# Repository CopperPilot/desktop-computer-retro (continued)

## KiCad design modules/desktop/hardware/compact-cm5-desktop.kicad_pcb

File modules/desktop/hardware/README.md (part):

# KiCad Project — Compact All-in-One CM5 Desktop Computer (`main` Carrier Board)

Generated from `rea/spec.yaml` by rea-hardware (fab rules, stackup, outline at the origin, mounting
holes), then completed by the electrical agent. Every placed part carries a verified `LCSC` field.

## 1. Component Rating & Margin Verification

| Component / Group | Net / Rail | Max Rail Voltage / Peak Current | Part MPN (`LCSC`) | Datasheet Rating | Margin Check |
|---|---|---|---|---|---|
| `C_PD_IN` | `VBUS_IN` (unswitched `J_PWR` VBUS) | 15.0 V nominal (24.4 V surge clamp) | `CC0805KKX7R9BB105` (`C91185`, 1 uF 50 V X7R 0805) | 50 V X7R | 50 V = 3.33x of 15 V (> 24.4 V TVS clamp); keeps unswitched `J_PWR` `cSnkVBus` = 1.0 uF direct (2.0 uF total including `C_PD_VHV` behind 1 kOhm `R_PD_VHV`), well below the 10 uF USB Type-C limit |
| `Q_PD_SW` + `R_PD_PG` + `R_PD_PG2` + `C_PD_SS` | `VBUS_IN` -> `VBUS_PD` (15 V PD) | 15.0 V / 1.85 A peak (24.4 V surge clamp) | `AO3407A` (`C347478`, SOT-23) + 2x `0402WGF1003TCE` (`C25741`, 100k) + `CL05B104KB54PNC` (`C307331`, 100 nF 50 V) | `AO3407A`: -30 V `V_DS`, ±20 V `V_GS`, -4.2 A continuous, `R_DS(on)` = 37 mOhm typ at -10 V / 42 mOhm at -7.5 V (`P_D` = 1.4 W) | `R_PD_PG`=100k and `R_PD_PG2`=100k set `V_GS` = -7.50 V at 15 V (-12.2 V max at 24.4 V TVS clamp << ±20 V `V_GS(max)`) with `tau_G` = 5.0 ms soft-start (`C_PD_SS`=100 nF), isolating 67.1 uF (`C_PD_BULK` + `C_VIN1..3`) until `U_PD` `PG` asserts low |
| `C_PD_BULK` | `VBUS_PD` (switched 15 V PD) | 15.0 V nominal (24.4 V surge clamp) | `CA55-D035K476TE150` (`C2761441`, 47 uF 35 V Case-D 7343 tantalum, 150 mOhm ESR) | 35 V MnO2 tantalum | 35 V = 2.33x of 15 V (> 24.4 V TVS clamp); isolated behind `Q_PD_SW` during hot-plug and PD negotiation |
| `C_VIN1`, `C_VIN2` | `VBUS_PD` (switched 15 V PD) | 15.0 V nominal (24.4 V surge clamp) | `HGC0805R5106K350NSLJ` (`C33546007`, 10 uF 0805) | 35 V X5R | 35 V >= 2.33x of 15 V (> 24.4 V TVS clamp); isolated behind `Q_PD_SW` until PD negotiation completes |
| `C_VIN3`, `C_BUCK_BST`, `C_BUCK_EN` | `VBUS_PD` / `BUCK_BST` / `BUCK_EN` | 15.0 V / 18.3 V / 2.5 V | `CL05B104KB54PNC` (`C307331`, 100 nF 0402) | 50 V X7R | 50 V >= 2.73x of 18.3 V (> 27.7 V surge) |
| `C_PD_VHV`, `C_BUCK_VREG` | `PD_VHV` / `BUCK_VREG5` | 14.2 V / 3.3 V | `CL10A105KB8NNNC` (`C15849`, 1 uF 0603) | 50 V / 25 V X5R | `C_PD_VHV` isolated from `VBUS_IN` via `R_PD_VHV` = 1 kOhm (`0402WGF1001TCE`, `C11702`) per CH224A datasheet |
| `C_5V1..C_5V3` | `5V_SYS` | 5.0 V max | `C2012X5R1A476MTJ00E` (`C76636`, 47 uF 0805) | 10 V X5R | 3x 47 uF = 141 uF nominal (~70 uF effective at 5 V) adjacent to `L_BUCK.2` / `U_BUCK.9` |
| `C_CM5_BULK` | `5V_SYS` (at `U_CM5` pins 77-87) | 5.0 V max | `SA11AM101A19R15XXX` (`C135491`, 100 uF Case-A polymer, 15 mOhm ESR) | 10 V solid polymer | 10 V = 2.0x of 5 V; buffers CM5 3.0 A load steps directly at mezzanine socket |
| `C_3V3_IN`, `C_3V3_OUT1`, `C_3V3_OUT2`, `C_BL_IN`, `C_3V3_1`, `C_KB_VBUS`, `C_MOUSE_VBUS` | `5V_SYS`, `3V3_SYS`, `3V3_CM5`, `5V_USB_*` | <= 5.0 V max | `HGC0805R5106K350NSLJ` (`C33546007`, 10 uF 0805) | 35 V X5R | 35 V >= 7.0x of 5 V (>= 1.5x required) |
| `C_BL_COMP` | `BL_COMP` | <= 3.3 V max | `TCC0402X7R224K250AT` (`C915854`, 220 nF 0402) | 25 V X7R | Matches TPS61165 datasheet 220 nF COMP requirement |
| `C_BL_OUT` | `BL_LED_A` (LED string) | ~9.9 V typ (38 V OVP) | `CC0805KKX7R9BB105` (`C91185`, 1 uF 50 V X7R 0805) | 50 V X7R | 50 V = 1.32x above 38 V OVP cutoff |
| `C_5V4`, `C_CM5_5V`, `C_3V3_2`, `C_3V3_3`, `C_3V3_HF`, `C_CM5_1V8`, `C_BOOT_VBUS`, `C_KB_DEC`, `C_MOUSE_DEC`, `C_CC_KB`, `C_CC_MOUSE`, `C_DSI_3V3`, `C_HDMI_5V` | `5V_SYS` / `3V3_SYS` / `3V3_CM5` / `1V8_CM5` | <= 5.0 V max | `CL05B104KB54PNC` (`C307331`, 100 nF 0402) | 50 V X7R | 50 V >= 10.0x of 5 V |
| `C_BUCK_SS` | `BUCK_SS` | 3.3 V max | `0402B223K500NT` (`C1532`, 22 nF 0402) | 50 V X7R | Programs `t_SS = 22 nF * 0.6 V / 6 uA = 2.2 ms` soft-start |
| `U_PD` + `R_PD_CFG1` + `R_PD_VHV` | `VBUS_IN`, `CC1`, `CC2`, `PD_CFG1`, `PD_VHV` | 15.0 V PD | `CH224A` (`C42459160`) + `RC0402FR-0756KL` (`C114756`, 56 kOhm 1%) + `0402WGF1001TCE` (`C11702`, 1 kOhm 1%) | 4 V to 30 V operating (`VHV` pin 1 fed from `VBUS_IN` via `R_PD_VHV` = 1 kOhm `C11702` + 1 uF `C_PD_VHV` per CH224A application circuit); `CFG1` (pin 9) strapped to `GND` via `R_PD_CFG1` = 56 kOhm 1% (`C114756`) to request mandatory 15 V USB-PD 3.0 fixed PDO | 30 V max > 24.4 V TVS clamp on 15 V rail; 56 kOhm requests 15 V (1.85 A peak at 27.71 W input < 3.0 A PDO limit) |
| `U_BUCK` + `L_BUCK` + `C_BUCK_EN` | `VBUS_PD` -> `5V_SYS` | 15.0 V in (24.4 V surge clamp), 5.0 V / 4.89 A peak | `SY8205FCC` (`C111875`) + `PSPMAA0503-4R7M-ANP` (`C436535`) + `CL05B104KB54PNC` (`C307331`) | 4.5-30 V recommended operating / 33 V abs max input, 5.0 A continuous / 6.0 A peak (`V_REF` = 0.600 V; `R_BUCK_FB1`=73.2k `C26986` / `R_BUCK_FB2`=10k `C25744` -> `V_OUT` = 4.992 V); `R_BUCK_EN1`=100k / `R_BUCK_EN2`=20k + `C_BUCK_EN`=100 nF on switched `VBUS_PD` sets `V_BUCK_EN` = 2.50 V at 15.0 V (`>= 2.38 V` at 14.25 V > `V_ENH` = 1.2 V) with `tau_EN` = 1.67 ms RC delay after `Q_PD_SW` charges `VBUS_PD` | 30 V rec / 33 V abs max safely exceeds `D_PD_VBUS` (`PTVS15VS1UR,115`, `V_BR`=16.7-18.5 V, `V_CL`=24.4 V at 16.4 A); `Q_PD_SW` isolates `VBUS_PD` until `U_PD.10` (`PG`) asserts |
| `U_3V3` + `L_3V3` + `Q_3V3_INV` + `Q_3V3_DIS` + `R_3V3_DIS` + `R_3V3_BLEED` + `D_3V3_CLAMP` + `U_SW_DSI` + `R_DSI_DIS` | `5V_SYS` -> `3V3_SYS` -> `3V3_DSI` | 3.3 V / 0.55 A peak (`front_io` + `J_DSI.22`) | `TLV62569DBVR` (`C141836`) + `SPH4018H2R2MT` (`C370436`, 2.2 uH) + 2x `BSS138` (`C78284`) + `0402WGF330JTCE` (`C25105`, 33R) + `0402WGF1001TCE` (`C11702`, 1k) + `B5819W` (`C2943878`) + `TPS2051BDBVR` (`C24593`) | `TLV62569DBVR`: 2.5-5.5 V in, 2.0 A out (`R_3V3_FB1`=100k `C25741` / `R_3V3_FB2`=22.1k `C43473` -> `V_OUT` = 3.31 V), enabled by `3V3_CM5`; active discharge (`Q_3V3_INV`/`Q_3V3_DIS` + `R_3V3_DIS`=33R + `R_3V3_BLEED`=1k, `tau` = 1.85 ms) and `D_3V3_CLAMP` (`B5819W` Anode `3V3_SYS` -> Cathode `3V3_CM5`) clamp `3V3_SYS <= 3V3_CM5 + 0.25 V` during shutdown/reset; `TPS2051BDBVR`: 500 mA soft-start load switch gating `J_DSI.22` (`3V3_DSI`) via `DSI1_EN` with `R_DSI_DIS`=1k (`C11702`) output bleeder and `R_DSI_SCL`/`R_DSI_SDA`=1.8k (`C25871`) referenced to switched `3V3_DSI` | Offloads `front_io` SD card and `J_DSI.22` LCD panel from `3V3_CM5`, prevents cross-domain GPIO back-drive during power-down, and eliminates I2C back-powering into `3V3_DSI` when `U_SW_DSI` is off |
| `U_BL` + `L_BL` + `D_BL` + `R_BL_SET` + `R_BL_FB` + `D_BL_FB` + `D_BL_A` | `5V_SYS` -> `BL_LED_A` / `BL_FB` | 9.9 V typ / 220 mA (3S11P WLED, 38 V OVP) | `TPS61165DBVR` (`C58756`) + `SWPA4030S220MT` (`C83472`) + `MBR0560` (`C77338`) + `0805W8F910LT5E` (`C17478`, 0.91 Ohm) + `0402WGF4701TCE` (`C25900`, 4.7k) + `PTVSLC3D3V3B` (`C246774`) + `PTVS36VS1UR,115` (`C171823`) | 38 V boost switch, 1.2 A switch limit, 60 V Schottky; `I_LED` = 0.200 V / 0.91 Ohm = 220 mA; `R_BL_FB` (4.7k) + `D_BL_FB` (3.3 V TVS) protects `U_BL.6` (`FB`, 3.6 V abs max) on 375 mm `J_BL` harness | `C_BL_IN`=10 uF and `C_BL_COMP`=220 nF meet TPS61165 datasheet; `BL_FB` and `BL_LED_A` protected against harness ESD/short faults |
| `U_SW_HDMI` | `5V_SYS` -> `5V_HDMI` (`J_HDMI.18`) | 5.0 V / 55 mA HDMI +5V Power | `AP2331SA-7` (`C500764`, SOT-23-3) | 0.2 A continuous / <= 0.4 A current-limited reverse-blocking load switch (`R_DS(on)` = 250 mOhm typ) | Maintains 4.986 V >= 4.8 V at 55 mA while enforcing <= 0.4 A short-circuit limit |
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
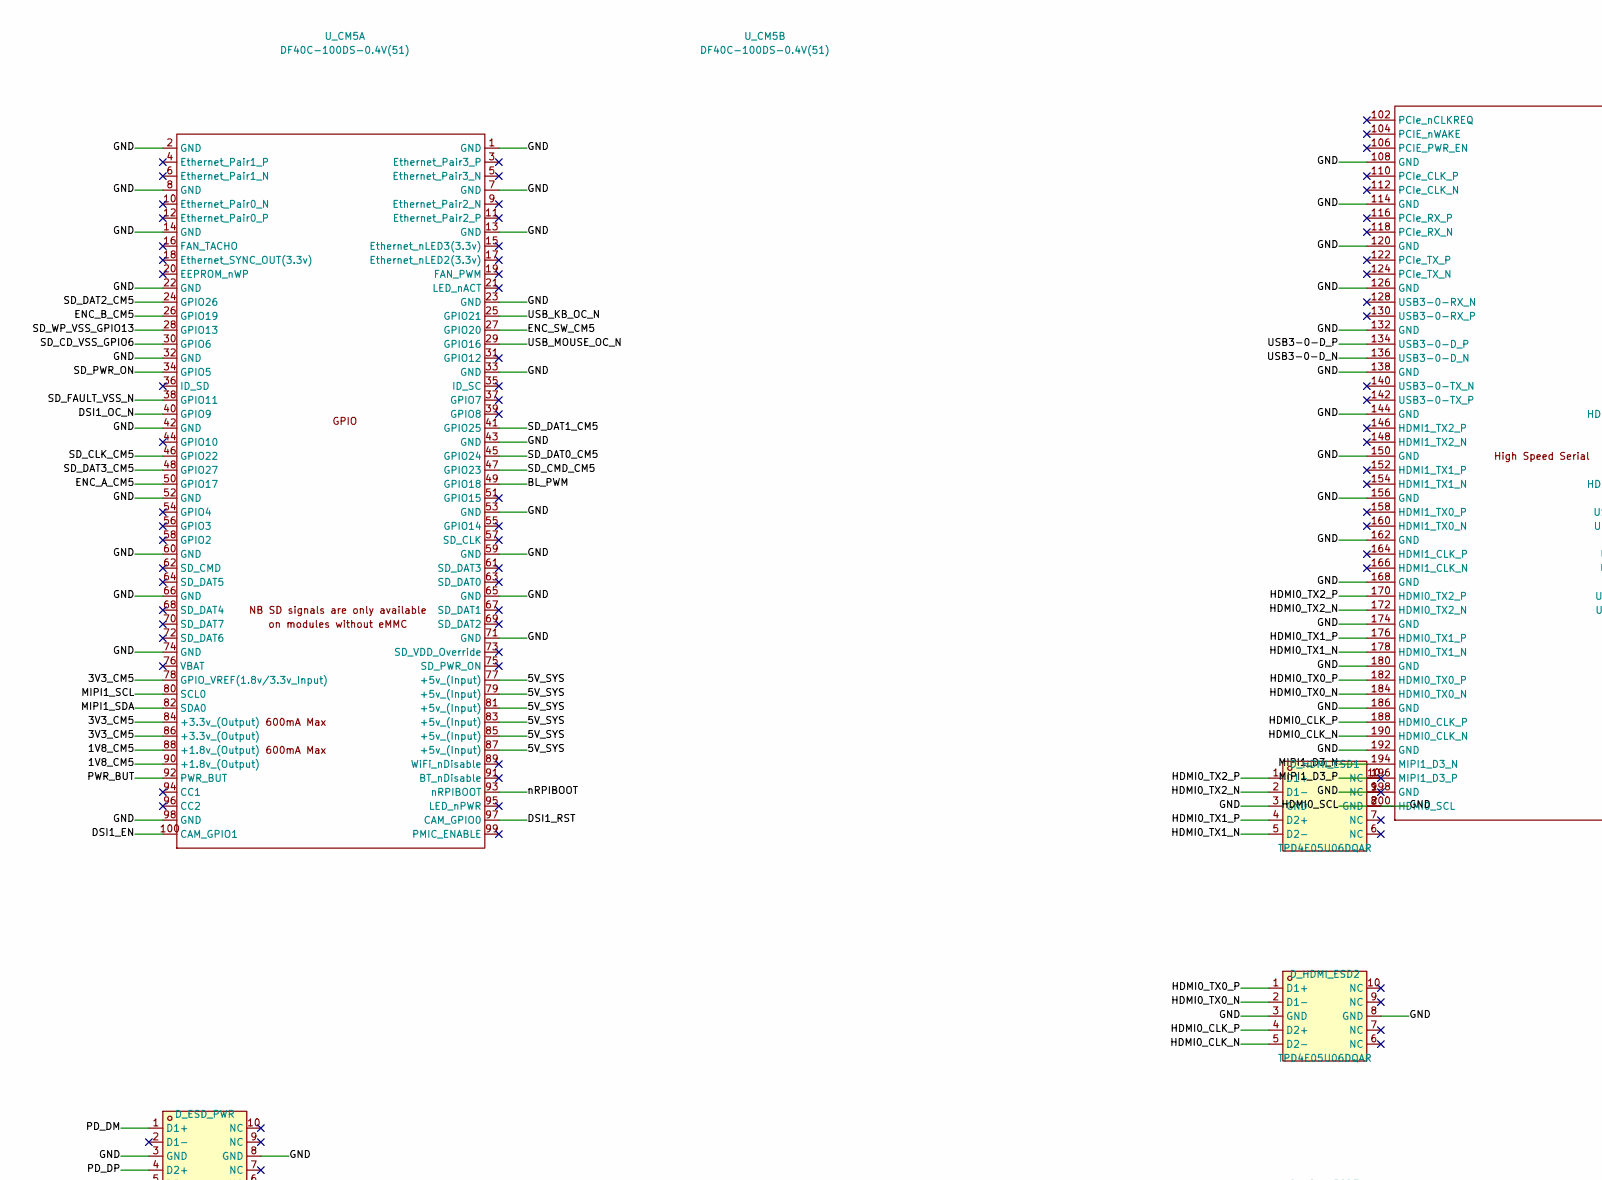
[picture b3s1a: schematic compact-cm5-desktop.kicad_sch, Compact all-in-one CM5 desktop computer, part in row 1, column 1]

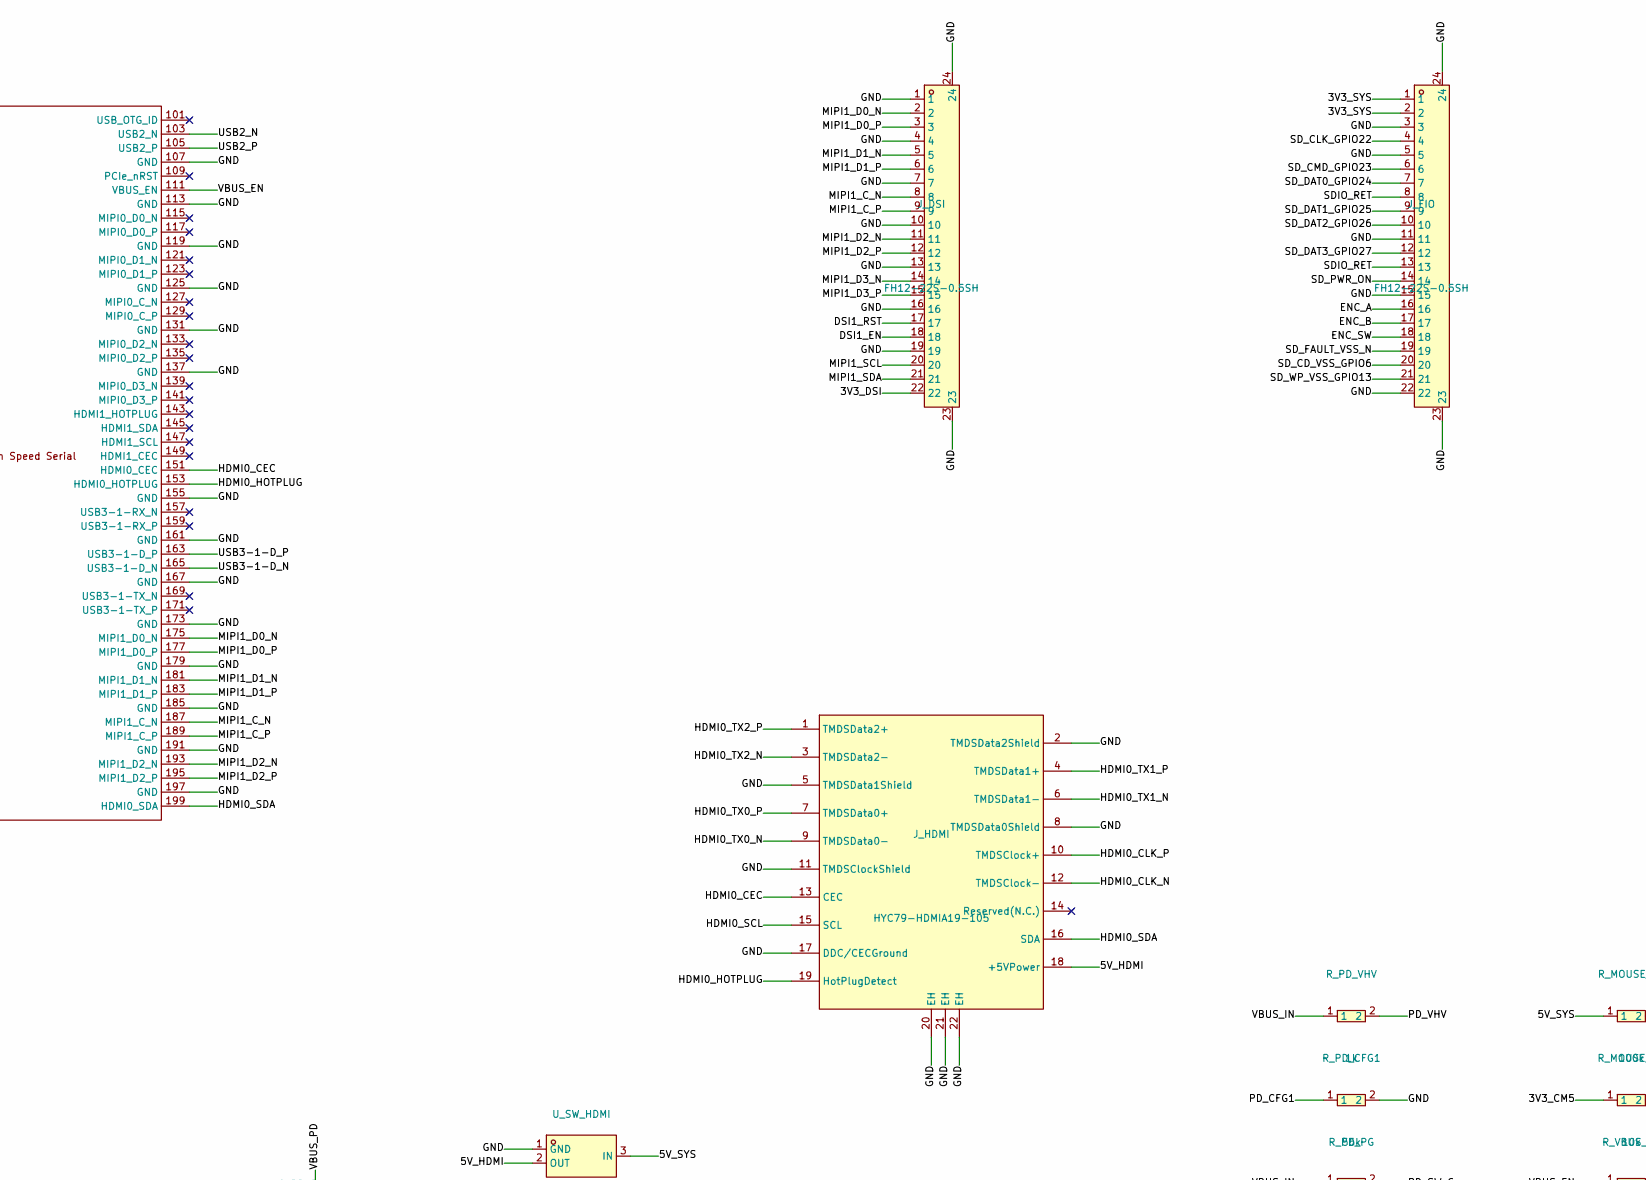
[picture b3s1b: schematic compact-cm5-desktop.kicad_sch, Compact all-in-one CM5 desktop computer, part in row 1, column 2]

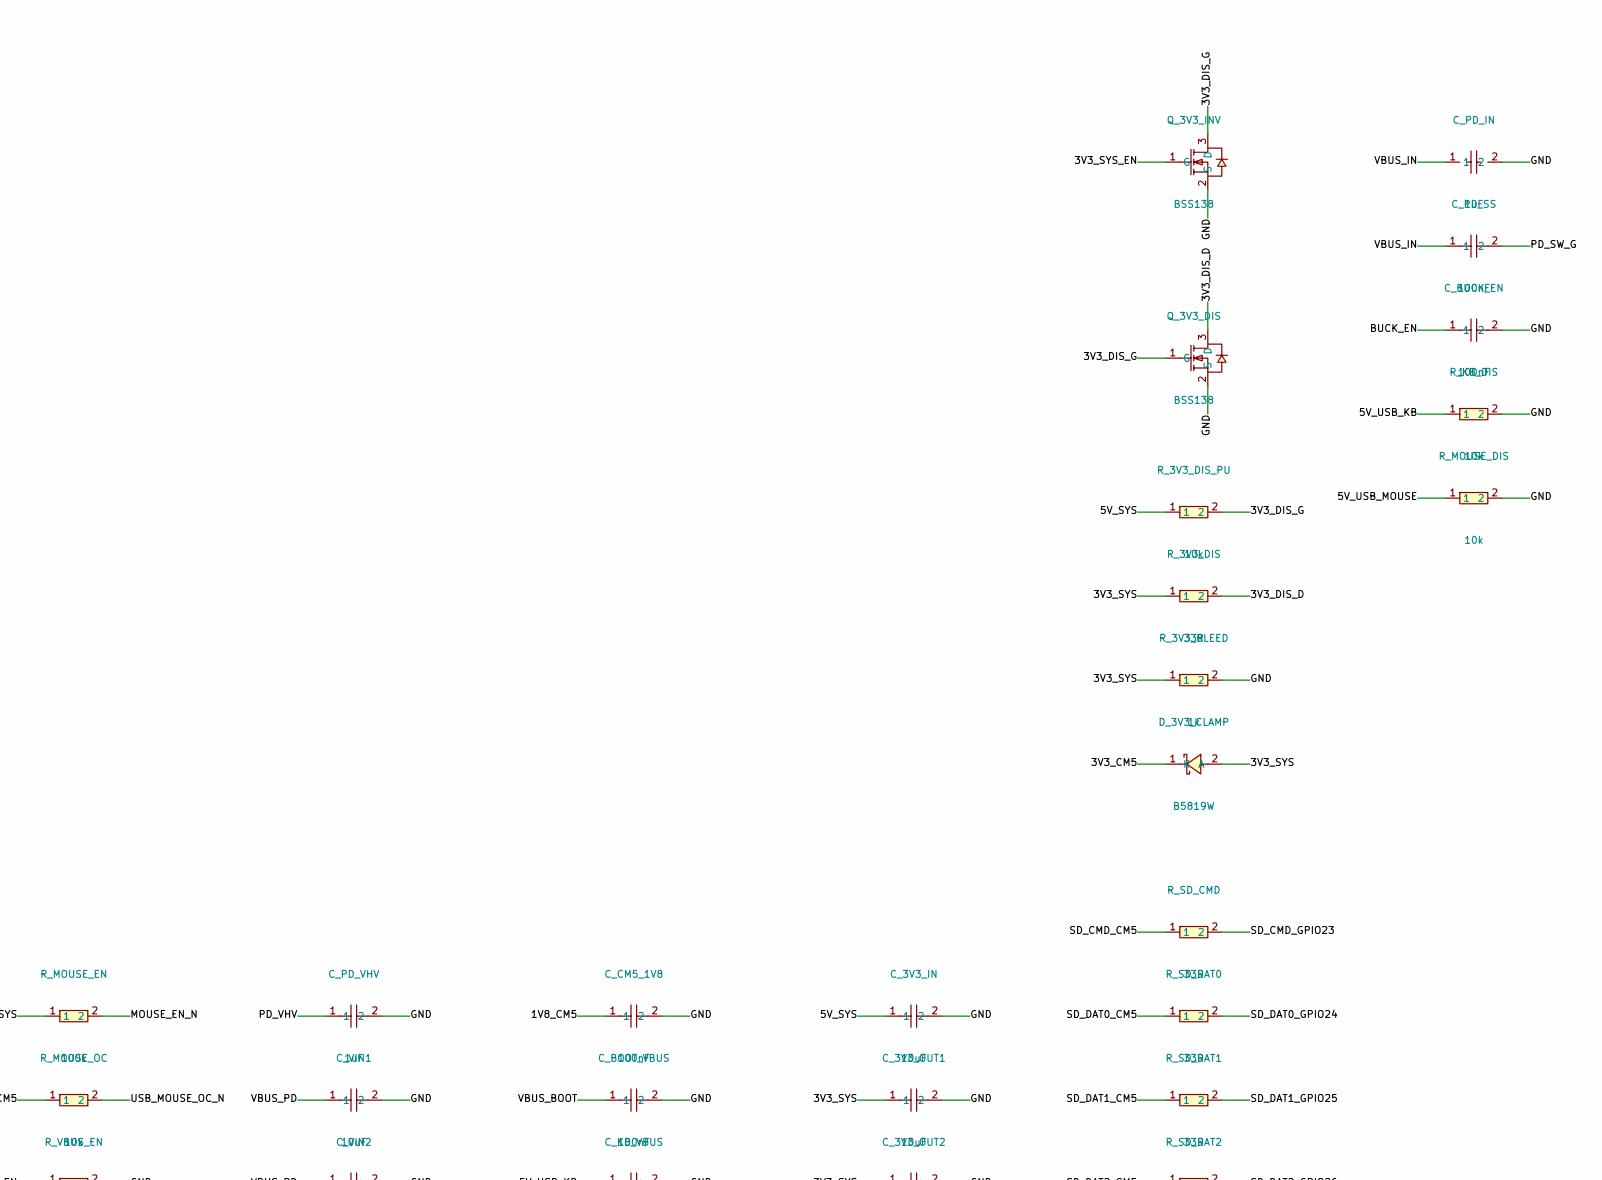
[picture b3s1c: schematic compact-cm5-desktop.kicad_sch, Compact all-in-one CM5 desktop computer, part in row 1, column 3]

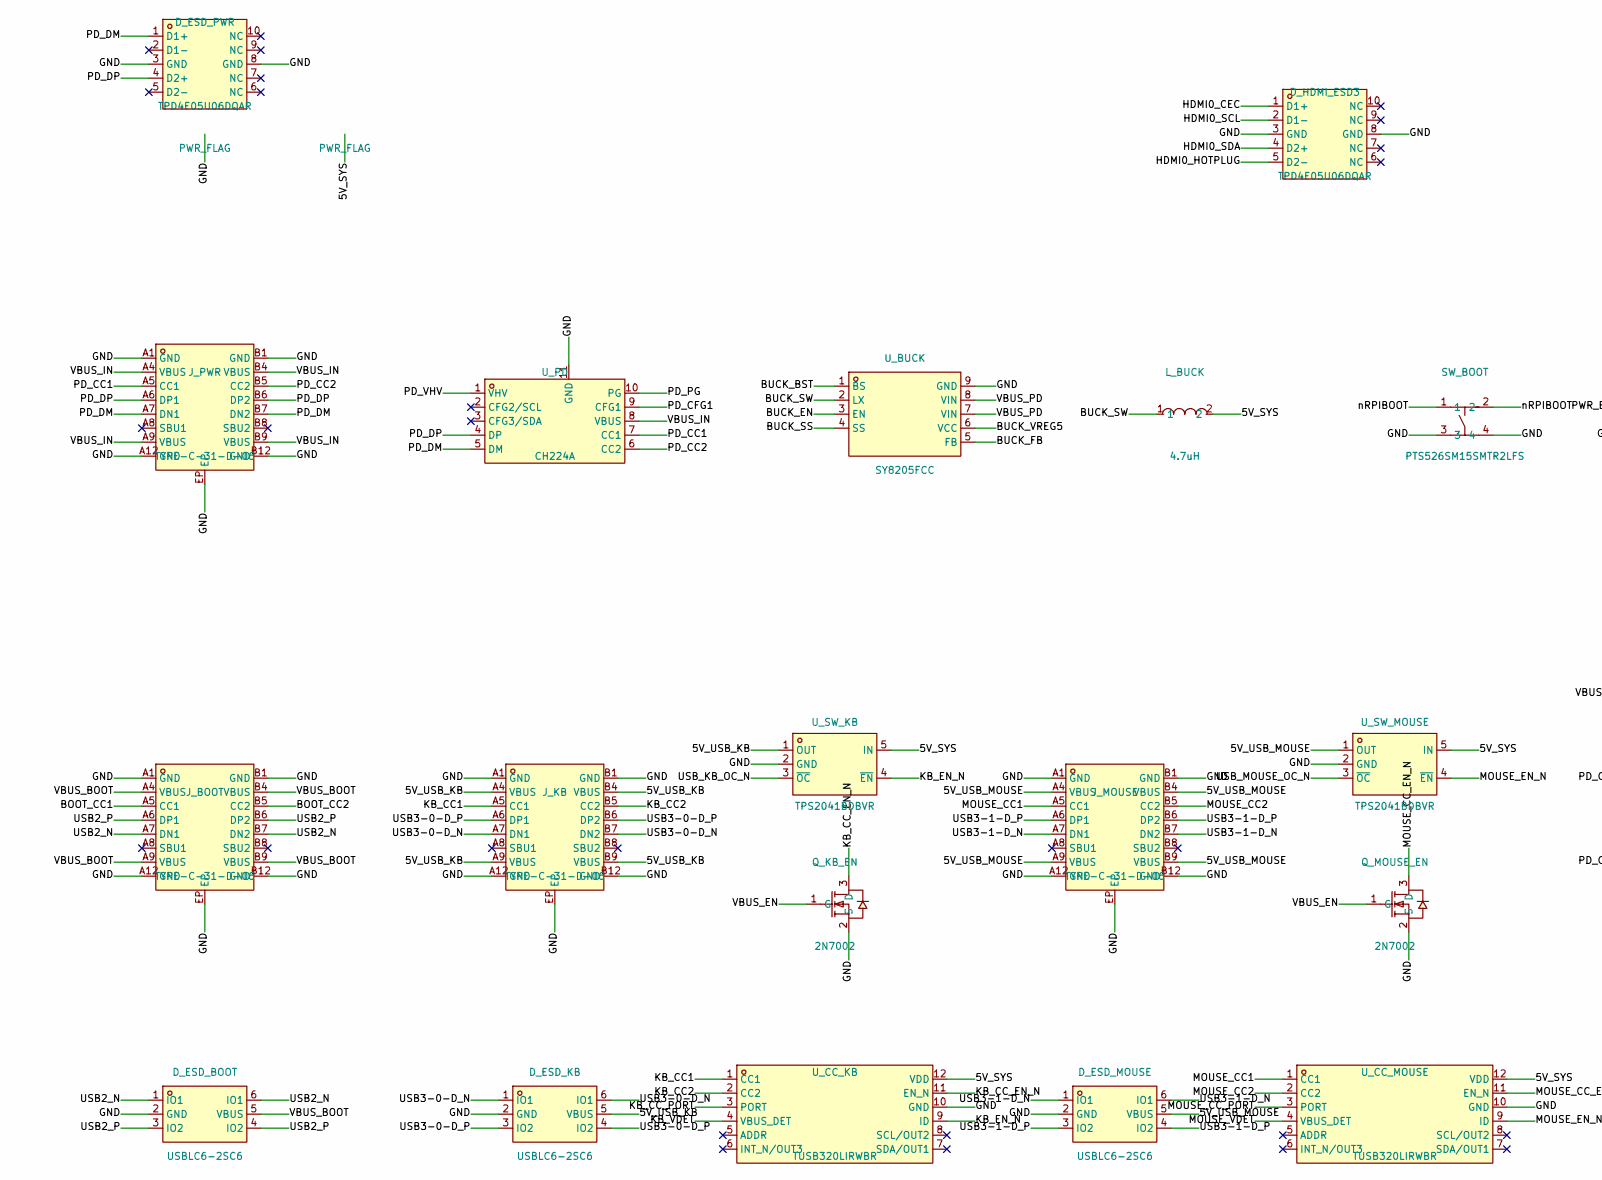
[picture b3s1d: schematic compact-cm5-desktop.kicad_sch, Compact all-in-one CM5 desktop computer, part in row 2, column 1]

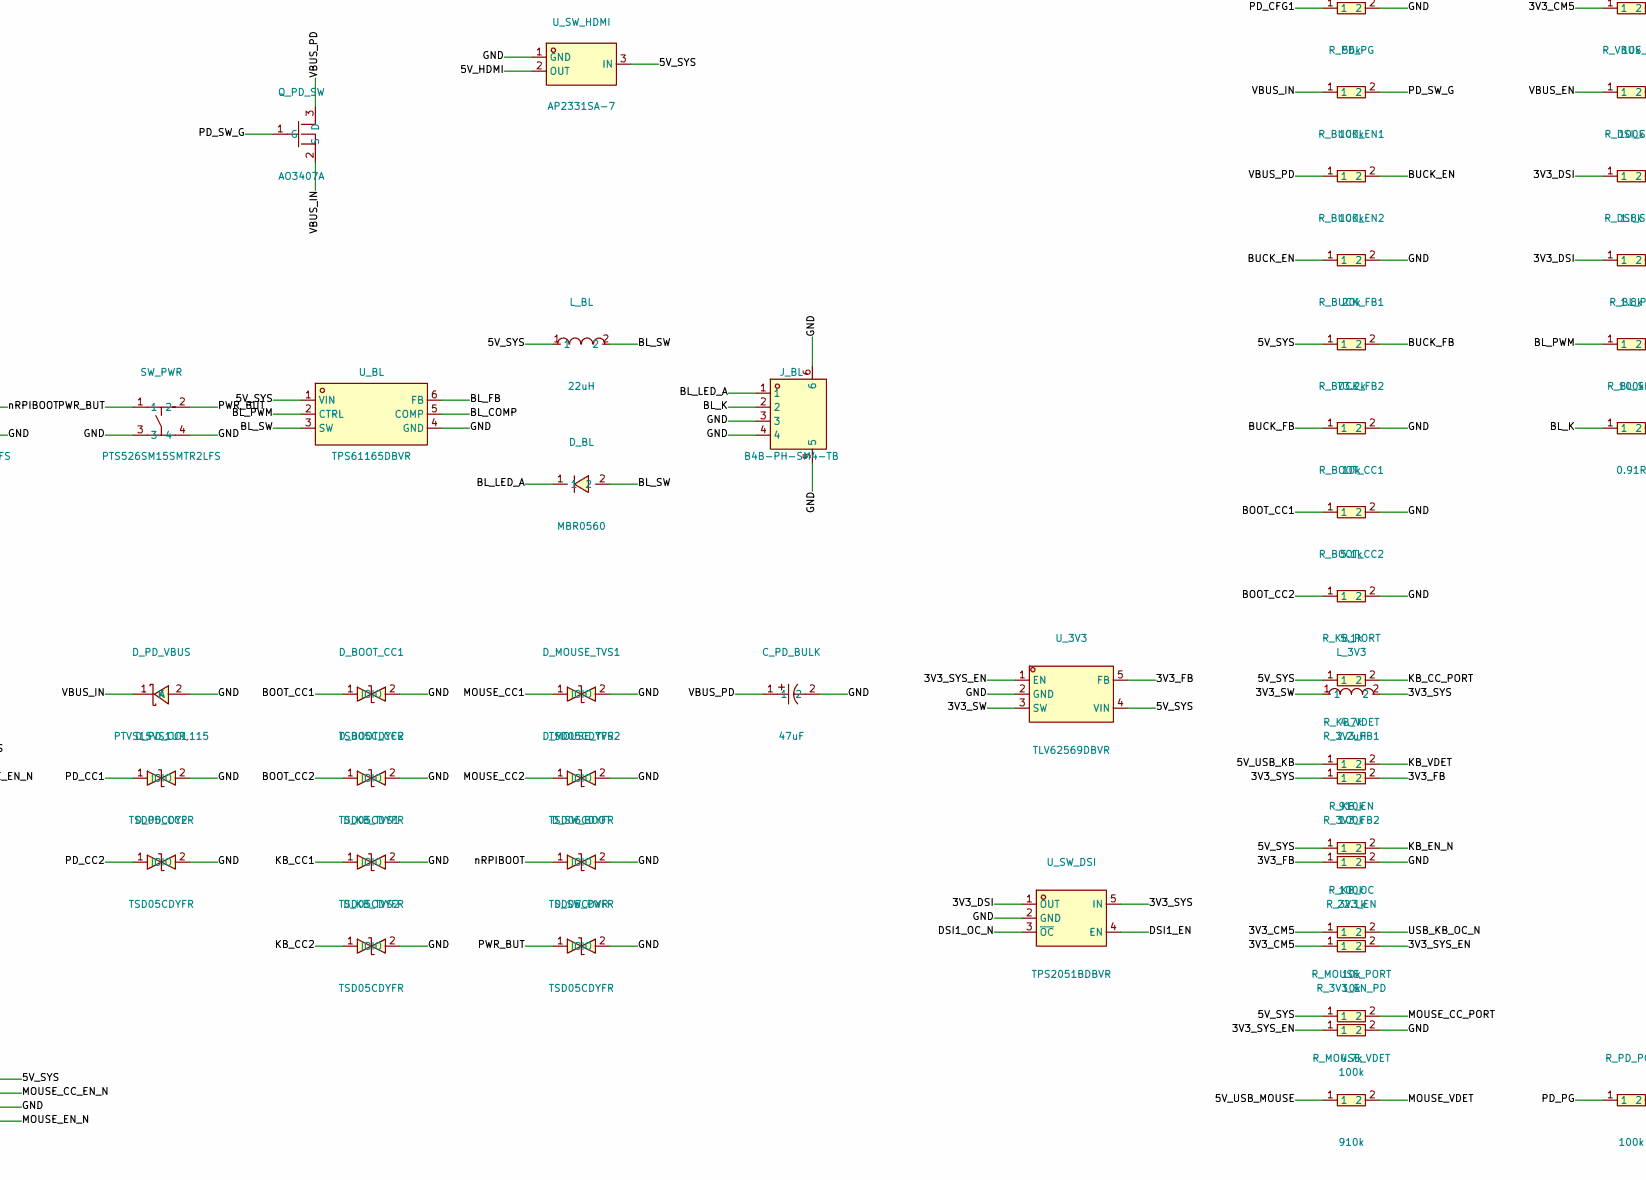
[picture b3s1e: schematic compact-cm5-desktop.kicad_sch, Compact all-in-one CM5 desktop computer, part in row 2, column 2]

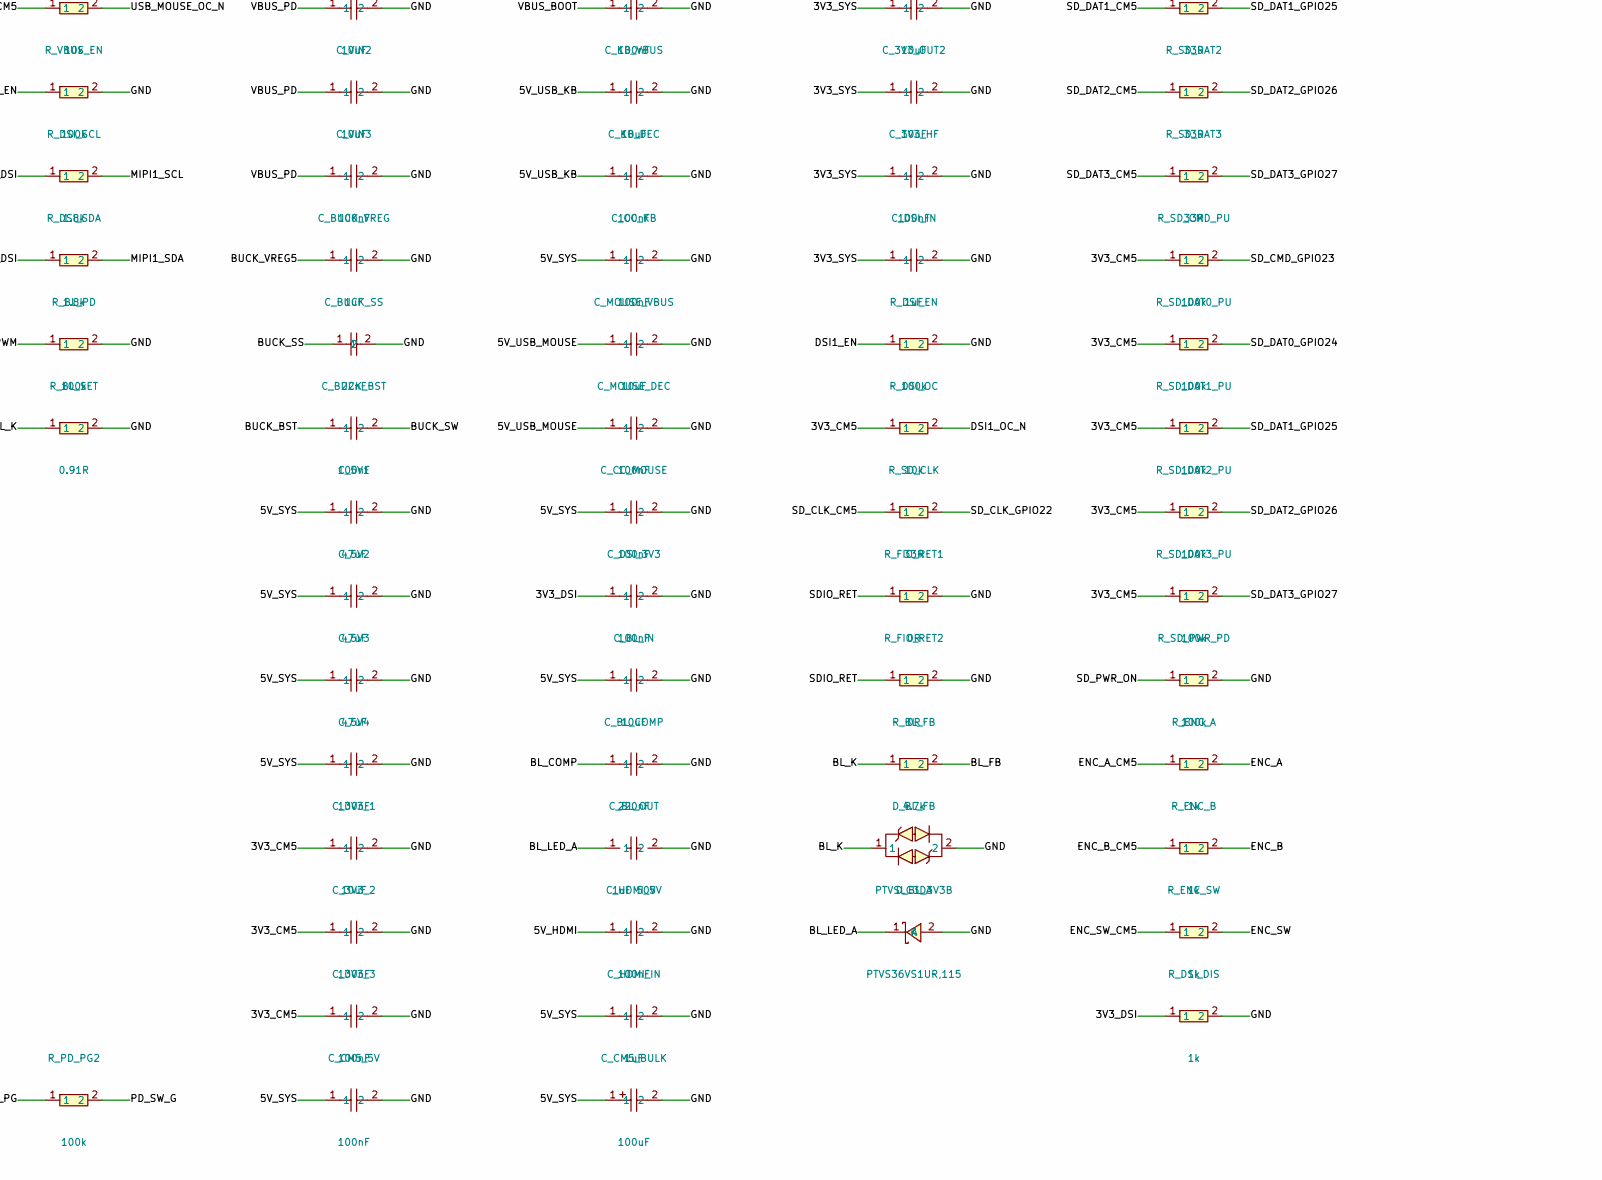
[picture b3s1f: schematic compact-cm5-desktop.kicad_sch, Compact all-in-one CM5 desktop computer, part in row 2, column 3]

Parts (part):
C_3V3_1, C_3V3_IN, C_3V3_OUT1, C_3V3_OUT2: 10uF; C0805; MPN HGC0805R5106K350NSLJ; LCSC C33546007
C_3V3_2, C_3V3_3, C_3V3_HF, C_5V4: 100nF; C0402; MPN CL05B104KB54PNC; LCSC C307331
C_5V1, C_5V2, C_5V3: 47uF; C0805; MPN C2012X5R1A476MTJ00E; LCSC C76636
C_BL_COMP: 220nF; C0402; MPN TCC0402X7R224K250AT; LCSC C915854
C_BL_IN: 10uF; C0805; MPN HGC0805R5106K350NSLJ; LCSC C33546007
C_BL_OUT: 1uF 50V; C0805; MPN CC0805KKX7R9BB105; LCSC C91185
C_BOOT_VBUS: 100nF; C0402; MPN CL05B104KB54PNC; LCSC C307331
C_BUCK_BST: 100nF; C0402; MPN CL05B104KB54PNC; LCSC C307331
C_BUCK_EN: 100nF; C0402; MPN CL05B104KB54PNC; LCSC C307331
C_BUCK_SS: 22nF; C0402; MPN 0402B223K500NT; LCSC C1532
C_BUCK_VREG: 1uF; C0603; MPN CL10A105KB8NNNC; LCSC C15849
C_CC_KB: 100nF; C0402; MPN CL05B104KB54PNC; LCSC C307331
C_CC_MOUSE: 100nF; C0402; MPN CL05B104KB54PNC; LCSC C307331
C_CM5_1V8, C_CM5_5V: 100nF; C0402; MPN CL05B104KB54PNC; LCSC C307331
C_CM5_BULK: 100uF; CAP-SMD_L7.3-W4.3_SA11CM470A19R55XXX; MPN SA11AM101A19R15XXX; LCSC C135491
C_DSI_3V3: 100nF; C0402; MPN CL05B104KB54PNC; LCSC C307331
C_DSI_IN: 1uF; C0603; MPN CL10A105KB8NNNC; LCSC C15849
C_HDMI_5V: 100nF; C0402; MPN CL05B104KB54PNC; LCSC C307331
C_HDMI_IN: 1uF; C0603; MPN CL10A105KB8NNNC; LCSC C15849
C_KB_DEC: 100nF; C0402; MPN CL05B104KB54PNC; LCSC C307331
C_KB_VBUS: 10uF; C0805; MPN HGC0805R5106K350NSLJ; LCSC C33546007
C_MOUSE_DEC: 100nF; C0402; MPN CL05B104KB54PNC; LCSC C307331
C_MOUSE_VBUS: 10uF; C0805; MPN HGC0805R5106K350NSLJ; LCSC C33546007
C_PD_BULK: 47uF; CAP-SMD_L7.3-W4.3-FD; MPN CA55-D035K476TE150; LCSC C2761441
C_PD_IN: 1uF; C0805; MPN CC0805KKX7R9BB105; LCSC C91185
C_PD_SS: 100nF; C0402; MPN CL05B104KB54PNC; LCSC C307331
C_PD_VHV: 1uF; C0603; MPN CL10A105KB8NNNC; LCSC C15849
C_VIN1, C_VIN2: 10uF; C0805; MPN HGC0805R5106K350NSLJ; LCSC C33546007
C_VIN3: 100nF; C0402; MPN CL05B104KB54PNC; LCSC C307331
D_3V3_CLAMP: B5819W; SOD-123F_L2.7-W1.6-LS3.8-RD-1; MPN B5819W; LCSC C2943878
D_BL: MBR0560; SOD-123_L2.8-W1.8-LS3.7-RD; MPN MBR0560; LCSC C77338
D_BL_A: PTVS36VS1UR,115; SOD-123_L2.6-W1.7-LS3.5-RD; MPN PTVS36VS1UR,115; LCSC C171823
D_BL_FB: PTVSLC3D3V3B; SOD-323_L1.8-W1.3-LS2.5-BI; MPN PTVSLC3D3V3B; LCSC C246774
D_BOOT_CC1, D_BOOT_CC2: TSD05CDYFR; SOD-323_L1.8-W1.3-LS2.5-BI; MPN TSD05CDYFR; LCSC C20611048
D_ESD_BOOT: USBLC6-2SC6; SOT-23-6_L2.9-W1.6-P0.95-LS2.8-BL; MPN USBLC6-2SC6; LCSC C2827654
D_ESD_KB: USBLC6-2SC6; SOT-23-6_L2.9-W1.6-P0.95-LS2.8-BL; MPN USBLC6-2SC6; LCSC C2827654
D_ESD_MOUSE: USBLC6-2SC6; SOT-23-6_L2.9-W1.6-P0.95-LS2.8-BL; MPN USBLC6-2SC6; LCSC C2827654
D_ESD_PWR: TPD4E05U06DQAR; USON-10_L2.5-W1.0-P0.50-BL; MPN TPD4E05U06DQAR; LCSC C138714
D_HDMI_ESD1, D_HDMI_ESD2, D_HDMI_ESD3: TPD4E05U06DQAR; USON-10_L2.5-W1.0-P0.50-BL; MPN TPD4E05U06DQAR; LCSC C138714
D_KB_TVS1, D_KB_TVS2: TSD05CDYFR; SOD-323_L1.8-W1.3-LS2.5-BI; MPN TSD05CDYFR; LCSC C20611048
D_MOUSE_TVS1, D_MOUSE_TVS2: TSD05CDYFR; SOD-323_L1.8-W1.3-LS2.5-BI; MPN TSD05CDYFR; LCSC C20611048
D_PD_CC1, D_PD_CC2: TSD05CDYFR; SOD-323_L1.8-W1.3-LS2.5-BI; MPN TSD05CDYFR; LCSC C20611048
D_PD_VBUS: PTVS15VS1UR,115; SOD-123_L2.6-W1.7-LS3.5-RD; MPN PTVS15VS1UR,115; LCSC C513104
D_SW_BOOT: TSD05CDYFR; SOD-323_L1.8-W1.3-LS2.5-BI; MPN TSD05CDYFR; LCSC C20611048
D_SW_PWR: TSD05CDYFR; SOD-323_L1.8-W1.3-LS2.5-BI; MPN TSD05CDYFR; LCSC C20611048
J_BL: B4B-PH-SM4-TB; CONN-SMD_B4B-PH-SM4-TB-LF-SN; MPN B4B-PH-SM4-TB(LF)(SN); LCSC C160354
J_BOOT: TYPE-C-31-D-06; USB-C-SMD_TYPE-C-31-D-06; MPN TYPE-C-31-D-06; LCSC C2689964
J_DSI: FH12-22S-0.5SH; FPC-SMD_22P-P0.50_FH12-22S-0.5SH-55; MPN FH12-22S-0.5SH(55); LCSC C597981
J_FIO: FH12-22S-0.5SH; FPC-SMD_22P-P0.50_FH12-22S-0.5SH-55; MPN FH12-22S-0.5SH(55); LCSC C597981
J_HDMI: HYC79-HDMIA19-105; HDMI-SMD_HYC79-HDMIA19-105; MPN HYC79-HDMIA19-105; LCSC C711353
J_KB: TYPE-C-31-D-06; USB-C-SMD_TYPE-C-31-D-06; MPN TYPE-C-31-D-06; LCSC C2689964
J_MOUSE: TYPE-C-31-D-06; USB-C-SMD_TYPE-C-31-D-06; MPN TYPE-C-31-D-06; LCSC C2689964
J_PWR: TYPE-C-31-D-06; USB-C-SMD_TYPE-C-31-D-06; MPN TYPE-C-31-D-06; LCSC C2689964
L_3V3: 2.2uH; IND-SMD_L4.0-W4.0; MPN SPH4018H2R2MT; LCSC C370436
L_BL: 22uH; IND-SMD_L4.0-W4.0_SLW4010S; MPN SWPA4030S220MT; LCSC C83472
L_BUCK: 4.7uH; IND-SMD_L5.4-W5.2; MPN PSPMAA0503-4R7M-ANP; LCSC C436535
Q_3V3_DIS, Q_3V3_INV: BSS138; SOT-23-3_L2.9-W1.3-P1.90-LS2.4-BR; MPN BSS138; LCSC C78284
Q_KB_EN: 2N7002; SOT-23-3_L2.9-W1.3-P1.90-LS2.4-BR; MPN 2N7002; LCSC C8545
Q_MOUSE_EN: 2N7002; SOT-23-3_L2.9-W1.3-P1.90-LS2.4-BR; MPN 2N7002; LCSC C8545
Q_PD_SW: AO3407A; SOT-23_L2.9-W1.3-P1.90-LS2.4-BR; MPN AO3407A; LCSC C347478
R_3V3_BLEED: 1k; R0402; MPN 0402WGF1001TCE; LCSC C11702
R_3V3_DIS: 33R; R0402; MPN 0402WGF330JTCE; LCSC C25105
R_3V3_DIS_PU, R_3V3_EN: 10k; R0402; MPN 0402WGF1002TCE; LCSC C25744
R_3V3_EN_PD, R_3V3_FB1: 100k; R0402; MPN 0402WGF1003TCE; LCSC C25741
R_3V3_FB2: 22.1k; R0402; MPN 0402WGF2212TCE; LCSC C43473
R_BL_FB: 4.7k; R0402; MPN 0402WGF4701TCE; LCSC C25900
R_BL_PD: 100k; R0402; MPN 0402WGF1003TCE; LCSC C25741
R_BL_SET: 0.91R; R0805; MPN 0805W8F910LT5E; LCSC C17478
R_BOOT_CC1, R_BOOT_CC2: 5.1k; R0402; MPN 0402WGF5101TCE; LCSC C25905
R_BUCK_EN1: 100k; R0402; MPN 0402WGF1003TCE; LCSC C25741
R_BUCK_EN2: 20k; R0402; MPN 0402WGF2002TCE; LCSC C25765
R_BUCK_FB1: 73.2k; R0402; MPN 0402WGF7322TCE; LCSC C26986
R_BUCK_FB2: 10k; R0402; MPN 0402WGF1002TCE; LCSC C25744
R_DSI_DIS: 1k; R0402; MPN 0402WGF1001TCE; LCSC C11702
R_DSI_EN: 100k; R0402; MPN 0402WGF1003TCE; LCSC C25741
R_DSI_OC: 10k; R0402; MPN 0402WGF1002TCE; LCSC C25744
R_DSI_SCL: 1.8k; R0402; MPN 0402WGF1801TCE; LCSC C25871
R_DSI_SDA: 1.8k; R0402; MPN 0402WGF1801TCE; LCSC C25871
R_ENC_A: 1k; R0402; MPN 0402WGF1001TCE; LCSC C11702
R_ENC_B: 1k; R0402; MPN 0402WGF1001TCE; LCSC C11702
R_ENC_SW: 1k; R0402; MPN 0402WGF1001TCE; LCSC C11702
R_FIO_RET1, R_FIO_RET2: 0R; R0402; MPN 0402WGF0000TCE; LCSC C17168
R_KB_DIS: 10k; R0402; MPN 0402WGF1002TCE; LCSC C25744
R_KB_EN: 100k; R0402; MPN 0402WGF1003TCE; LCSC C25741
R_KB_OC: 10k; R0402; MPN 0402WGF1002TCE; LCSC C25744
R_KB_PORT: 4.7k; R0402; MPN 0402WGF4701TCE; LCSC C25900
R_KB_VDET: 910k; R0402; MPN 0402WGF9103TCE; LCSC C25800
R_MOUSE_DIS: 10k; R0402; MPN 0402WGF1002TCE; LCSC C25744
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
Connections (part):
/1V8_CM5: C_CM5_1V8.1, U_CM5.88 (+1.8v_(Output)), U_CM5.90 (+1.8v_(Output))
/3V3_CM5: C_3V3_1.1, C_3V3_2.1, C_3V3_3.1, D_3V3_CLAMP.1 (K), R_3V3_EN.1, R_DSI_OC.1, R_KB_OC.1, R_MOUSE_OC.1, R_SD_CMD_PU.1, R_SD_DAT0_PU.1, R_SD_DAT1_PU.1, R_SD_DAT2_PU.1, R_SD_DAT3_PU.1, U_CM5.78 (GPIO_VREF(1.8v/3.3v_Input)), U_CM5.84 (+3.3v_(Output)), U_CM5.86 (+3.3v_(Output))
/3V3_DIS_D: Q_3V3_DIS.3 (D), R_3V3_DIS.2
/3V3_DIS_G: Q_3V3_DIS.1 (G), Q_3V3_INV.3 (D), R_3V3_DIS_PU.2
/3V3_DSI: C_DSI_3V3.1, J_DSI.22, R_DSI_DIS.1, R_DSI_SCL.1, R_DSI_SDA.1, U_SW_DSI.1 (OUT)
/3V3_FB: R_3V3_FB1.2, R_3V3_FB2.1, U_3V3.5 (FB)
/3V3_SW: L_3V3.1, U_3V3.3 (SW)
/3V3_SYS: C_3V3_HF.1, C_3V3_OUT1.1, C_3V3_OUT2.1, C_DSI_IN.1, D_3V3_CLAMP.2 (A), J_FIO.1, J_FIO.2, L_3V3.2, R_3V3_BLEED.1, R_3V3_DIS.1, R_3V3_FB1.1, U_SW_DSI.5 (IN)
/3V3_SYS_EN: Q_3V3_INV.1 (G), R_3V3_EN.2, R_3V3_EN_PD.1, U_3V3.1 (EN)
/5V_HDMI: C_HDMI_5V.1, J_HDMI.18 (+5VPower), U_SW_HDMI.2 (OUT)
/5V_SYS: C_3V3_IN.1, C_5V1.1, C_5V2.1, C_5V3.1, C_5V4.1, C_BL_IN.1, C_CC_KB.1, C_CC_MOUSE.1, C_CM5_5V.1, C_CM5_BULK.1, C_HDMI_IN.1, L_BL.1, L_BUCK.2, R_3V3_DIS_PU.1, R_BUCK_FB1.1, R_KB_EN.1, R_KB_PORT.1, R_MOUSE_EN.1, R_MOUSE_PORT.1, U_3V3.4 (VIN), U_BL.1 (VIN), U_CC_KB.12 (VDD), U_CC_MOUSE.12 (VDD), U_CM5.77 (+5v_(Input)), U_CM5.79 (+5v_(Input)), U_CM5.81 (+5v_(Input)), U_CM5.83 (+5v_(Input)), U_CM5.85 (+5v_(Input)), U_CM5.87 (+5v_(Input)), U_SW_HDMI.3 (IN), U_SW_KB.5 (IN), U_SW_MOUSE.5 (IN)
/5V_USB_KB: C_KB_DEC.1, C_KB_VBUS.1, D_ESD_KB.5 (VBUS), J_KB.A4 (VBUS), J_KB.A9 (VBUS), J_KB.B4 (VBUS), J_KB.B9 (VBUS), R_KB_DIS.1, R_KB_VDET.1, U_SW_KB.1 (OUT)
/5V_USB_MOUSE: C_MOUSE_DEC.1, C_MOUSE_VBUS.1, D_ESD_MOUSE.5 (VBUS), J_MOUSE.A4 (VBUS), J_MOUSE.A9 (VBUS), J_MOUSE.B4 (VBUS), J_MOUSE.B9 (VBUS), R_MOUSE_DIS.1, R_MOUSE_VDET.1, U_SW_MOUSE.1 (OUT)
/BL_COMP: C_BL_COMP.1, U_BL.5 (COMP)
/BL_FB: R_BL_FB.2, U_BL.6 (FB)
/BL_K: D_BL_FB.1, J_BL.2, R_BL_FB.1, R_BL_SET.1
/BL_LED_A: C_BL_OUT.1, D_BL.1, D_BL_A.1 (K), J_BL.1
/BL_PWM: R_BL_PD.1, U_BL.2 (CTRL), U_CM5.49 (GPIO18)
/BL_SW: D_BL.2, L_BL.2, U_BL.3 (SW)
/BOOT_CC1: D_BOOT_CC1.1, J_BOOT.A5 (CC1), R_BOOT_CC1.1
/BOOT_CC2: D_BOOT_CC2.1, J_BOOT.B5 (CC2), R_BOOT_CC2.1
/BUCK_BST: C_BUCK_BST.1, U_BUCK.1 (BS)
/BUCK_EN: C_BUCK_EN.1, R_BUCK_EN1.2, R_BUCK_EN2.1, U_BUCK.3 (EN)
/BUCK_FB: R_BUCK_FB1.2, R_BUCK_FB2.1, U_BUCK.5 (FB)
/BUCK_SS: C_BUCK_SS.1, U_BUCK.4 (SS)
/BUCK_SW: C_BUCK_BST.2, L_BUCK.1, U_BUCK.2 (LX)
/BUCK_VREG5: C_BUCK_VREG.1, U_BUCK.6 (VCC)
/DSI1_EN: J_DSI.18, R_DSI_EN.1, U_CM5.100 (CAM_GPIO1), U_SW_DSI.4 (EN)
/DSI1_OC_N: R_DSI_OC.2, U_CM5.40 (GPIO9), U_SW_DSI.3 (~OC)
/DSI1_RST: J_DSI.17, U_CM5.97 (CAM_GPIO0)
/ENC_A: J_FIO.16, R_ENC_A.2
/ENC_A_CM5: R_ENC_A.1, U_CM5.50 (GPIO17)
/ENC_B: J_FIO.17, R_ENC_B.2
/ENC_B_CM5: R_ENC_B.1, U_CM5.26 (GPIO19)
/ENC_SW: J_FIO.18, R_ENC_SW.2
/ENC_SW_CM5: R_ENC_SW.1, U_CM5.27 (GPIO20)
/GND: C_3V3_1.2, C_3V3_2.2, C_3V3_3.2, C_3V3_HF.2, C_3V3_IN.2, C_3V3_OUT1.2, C_3V3_OUT2.2, C_5V1.2, C_5V2.2, C_5V3.2, C_5V4.2, C_BL_COMP.2, C_BL_IN.2, C_BL_OUT.2, C_BOOT_VBUS.2, C_BUCK_EN.2, C_BUCK_SS.2, C_BUCK_VREG.2, C_CC_KB.2, C_CC_MOUSE.2, C_CM5_1V8.2, C_CM5_5V.2, C_CM5_BULK.2, C_DSI_3V3.2, C_DSI_IN.2, C_HDMI_5V.2, C_HDMI_IN.2, C_KB_DEC.2, C_KB_VBUS.2, C_MOUSE_DEC.2, C_MOUSE_VBUS.2, C_PD_BULK.2, C_PD_IN.2, C_PD_VHV.2, C_VIN1.2, C_VIN2.2, C_VIN3.2, D_BL_A.2 (A), D_BL_FB.2, D_BOOT_CC1.2, D_BOOT_CC2.2, D_ESD_BOOT.2 (GND), D_ESD_KB.2 (GND), D_ESD_MOUSE.2 (GND), D_ESD_PWR.3 (GND), D_ESD_PWR.8 (GND), D_HDMI_ESD1.3 (GND), D_HDMI_ESD1.8 (GND), D_HDMI_ESD2.3 (GND), D_HDMI_ESD2.8 (GND), D_HDMI_ESD3.3 (GND), D_HDMI_ESD3.8 (GND), D_KB_TVS1.2, D_KB_TVS2.2, D_MOUSE_TVS1.2, D_MOUSE_TVS2.2, D_PD_CC1.2, D_PD_CC2.2, D_PD_VBUS.2 (A), D_SW_BOOT.2, D_SW_PWR.2, J_BL.3, J_BL.4, J_BL.5, J_BL.6, J_BOOT.A1 (GND), J_BOOT.A12 (GND), J_BOOT.B1 (GND), J_BOOT.B12 (GND), J_BOOT.EP, J_DSI.1, J_DSI.4, J_DSI.7, J_DSI.10, J_DSI.13, J_DSI.16, J_DSI.19, J_DSI.23, J_DSI.24, J_FIO.3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
/HDMI0_CEC: D_HDMI_ESD3.1 (D1+), J_HDMI.13 (CEC), U_CM5.151 (HDMI0_CEC)
/HDMI0_CLK_N: D_HDMI_ESD2.5 (D2-), J_HDMI.12 (TMDSClock-), U_CM5.190 (HDMI0_CLK_N)
/HDMI0_CLK_P: D_HDMI_ESD2.4 (D2+), J_HDMI.10 (TMDSClock+), U_CM5.188 (HDMI0_CLK_P)
/HDMI0_HOTPLUG: D_HDMI_ESD3.5 (D2-), J_HDMI.19 (HotPlugDetect), U_CM5.153 (HDMI0_HOTPLUG)
/HDMI0_SCL: D_HDMI_ESD3.2 (D1-), J_HDMI.15 (SCL), U_CM5.200 (HDMI0_SCL)
/HDMI0_SDA: D_HDMI_ESD3.4 (D2+), J_HDMI.16 (SDA), U_CM5.199 (HDMI0_SDA)
/HDMI0_TX0_N: D_HDMI_ESD2.2 (D1-), J_HDMI.9 (TMDSData0-), U_CM5.184 (HDMI0_TX0_N)
/HDMI0_TX0_P: D_HDMI_ESD2.1 (D1+), J_HDMI.7 (TMDSData0+), U_CM5.182 (HDMI0_TX0_P)
/HDMI0_TX1_N: D_HDMI_ESD1.5 (D2-), J_HDMI.6 (TMDSData1-), U_CM5.178 (HDMI0_TX1_N)
/HDMI0_TX1_P: D_HDMI_ESD1.4 (D2+), J_HDMI.4 (TMDSData1+), U_CM5.176 (HDMI0_TX1_P)
/HDMI0_TX2_N: D_HDMI_ESD1.2 (D1-), J_HDMI.3 (TMDSData2-), U_CM5.172 (HDMI0_TX2_N)
/HDMI0_TX2_P: D_HDMI_ESD1.1 (D1+), J_HDMI.1 (TMDSData2+), U_CM5.170 (HDMI0_TX2_P)
/KB_CC1: D_KB_TVS1.1, J_KB.A5 (CC1), U_CC_KB.1 (CC1)
/KB_CC2: D_KB_TVS2.1, J_KB.B5 (CC2), U_CC_KB.2 (CC2)
/KB_CC_EN_N: Q_KB_EN.3 (D), U_CC_KB.11 (EN_N)
/KB_CC_PORT: R_KB_PORT.2, U_CC_KB.3 (PORT)
/KB_EN_N: R_KB_EN.2, U_CC_KB.9 (ID), U_SW_KB.4 (~EN)
/KB_VDET: R_KB_VDET.2, U_CC_KB.4 (VBUS_DET)
/MIPI1_C_N: J_DSI.8, U_CM5.187 (MIPI1_C_N)
/MIPI1_C_P: J_DSI.9, U_CM5.189 (MIPI1_C_P)
/MIPI1_D0_N: J_DSI.2, U_CM5.175 (MIPI1_D0_N)
/MIPI1_D0_P: J_DSI.3, U_CM5.177 (MIPI1_D0_P)
/MIPI1_D1_N: J_DSI.5, U_CM5.181 (MIPI1_D1_N)
/MIPI1_D1_P: J_DSI.6, U_CM5.183 (MIPI1_D1_P)
/MIPI1_D2_N: J_DSI.11, U_CM5.193 (MIPI1_D2_N)
/MIPI1_D2_P: J_DSI.12, U_CM5.195 (MIPI1_D2_P)
/MIPI1_D3_N: J_DSI.14, U_CM5.194 (MIPI1_D3_N)
/MIPI1_D3_P: J_DSI.15, U_CM5.196 (MIPI1_D3_P)
/MIPI1_SCL: J_DSI.20, R_DSI_SCL.2, U_CM5.80 (SCL0)
/MIPI1_SDA: J_DSI.21, R_DSI_SDA.2, U_CM5.82 (SDA0)
/MOUSE_CC1: D_MOUSE_TVS1.1, J_MOUSE.A5 (CC1), U_CC_MOUSE.1 (CC1)
/MOUSE_CC2: D_MOUSE_TVS2.1, J_MOUSE.B5 (CC2), U_CC_MOUSE.2 (CC2)
/MOUSE_CC_EN_N: Q_MOUSE_EN.3 (D), U_CC_MOUSE.11 (EN_N)
/MOUSE_CC_PORT: R_MOUSE_PORT.2, U_CC_MOUSE.3 (PORT)
/MOUSE_EN_N: R_MOUSE_EN.2, U_CC_MOUSE.9 (ID), U_SW_MOUSE.4 (~EN)
/MOUSE_VDET: R_MOUSE_VDET.2, U_CC_MOUSE.4 (VBUS_DET)
/PD_CC1: D_PD_CC1.1, J_PWR.A5 (CC1), U_PD.7 (CC1)
/PD_CC2: D_PD_CC2.1, J_PWR.B5 (CC2), U_PD.6 (CC2)
/PD_CFG1: R_PD_CFG1.1, U_PD.9 (CFG1)
/PD_DM: D_ESD_PWR.1 (D1+), J_PWR.A7 (DN1), J_PWR.B7 (DN2), U_PD.5 (DM)
/PD_DP: D_ESD_PWR.4 (D2+), J_PWR.A6 (DP1), J_PWR.B6 (DP2), U_PD.4 (DP)
/PD_PG: R_PD_PG2.1, U_PD.10 (PG)
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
